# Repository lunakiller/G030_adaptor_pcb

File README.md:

# STM32G030F6P6 Adaptor PCB

Adaptor PCB for STM32G030F6P6. Contains power LED, 3.3V voltage regulator and SWD pin header for programming. 

All free pins are routed to the edge of the board.

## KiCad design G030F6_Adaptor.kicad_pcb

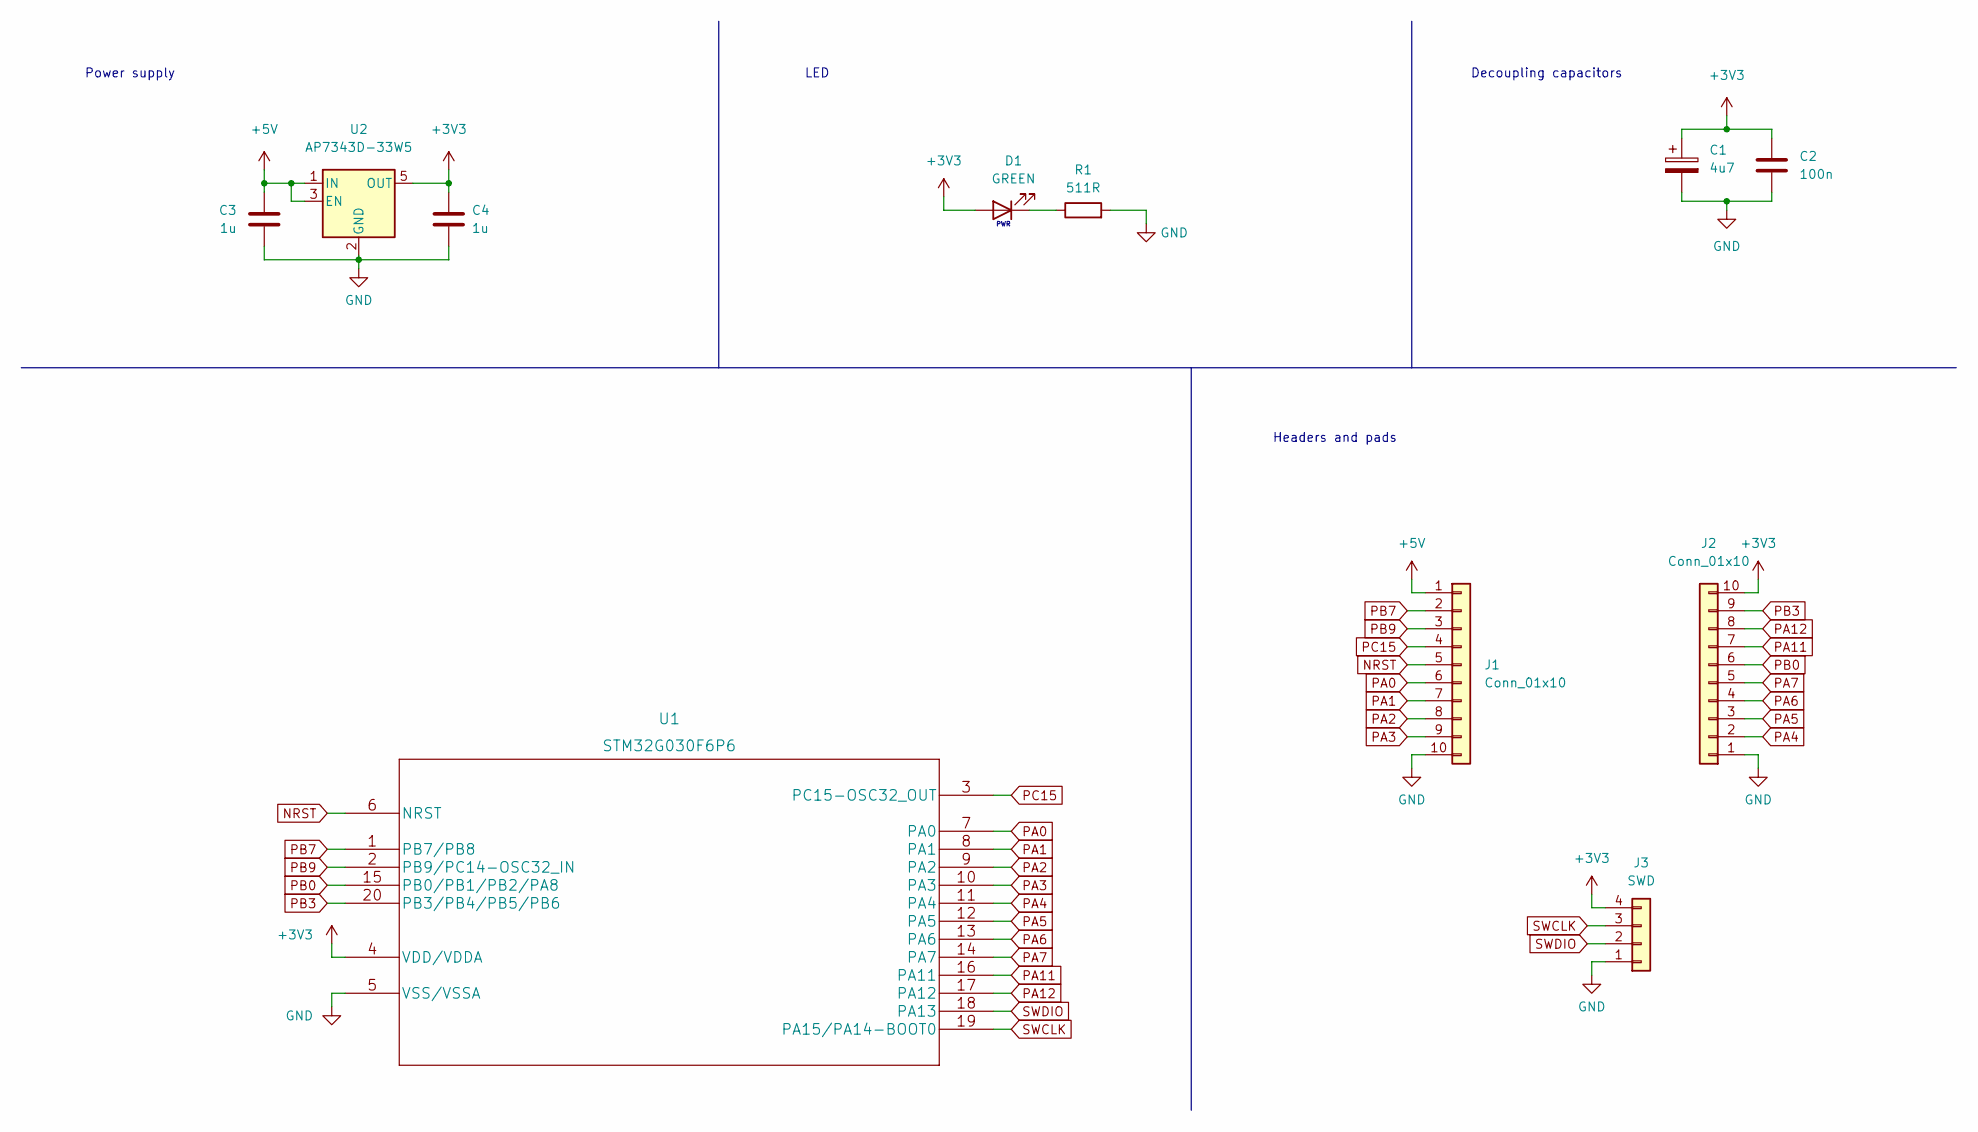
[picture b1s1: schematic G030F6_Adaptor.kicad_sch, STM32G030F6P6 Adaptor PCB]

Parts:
C1: 4u7; CP_EIA-1608-10_AVX-L
C2: 100n; C_0603_1608Metric
C3, C4: 1u; C_0603_1608Metric
D1: GREEN; LED_0603_1608Metric
J1, J2: Conn_01x10; PinHeader_Castellated_1x10_P2.54mm_Vertical
J3: SWD; PinHeader_1x04_P2.54mm_Vertical
R1: 511R; R_0603_1608Metric
U1: STM32G030F6P6; TSSOP-20_4.4x6.5mm_P0.65mm
U2: AP7343D-33W5; SOT-23-5

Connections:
+3V3: C1.1, C2.1, C4.1, D1.2 (A), J2.10, J3.4, U1.4 (VDD/VDDA), U2.5 (OUT)
+5V: C3.1, J1.1, U2.1 (IN), U2.3 (EN)
GND: C1.2, C2.2, C3.2, C4.2, J1.10, J2.1, J3.1, R1.2, U1.5 (VSS/VSSA), U2.2 (GND)
NRST: J1.5, U1.6 (NRST)
unnamed: D1.1 (K), R1.1
PA0: J1.6, U1.7 (PA0)
PA1: J1.7, U1.8 (PA1)
PA2: J1.8, U1.9 (PA2)
PA3: J1.9, U1.10 (PA3)
PA4: J2.2, U1.11 (PA4)
PA5: J2.3, U1.12 (PA5)
PA6: J2.4, U1.13 (PA6)
PA7: J2.5, U1.14 (PA7)
PA11: J2.7, U1.16 (PA11)
PA12: J2.8, U1.17 (PA12)
PB0: J2.6, U1.15 (PB0/PB1/PB2/PA8)
PB3: J2.9, U1.20 (PB3/PB4/PB5/PB6)
PB7: J1.2, U1.1 (PB7/PB8)
PB9: J1.3, U1.2 (PB9/PC14-OSC32_IN)
PC15: J1.4, U1.3 (PC15-OSC32_OUT)
SWCLK: J3.3, U1.19 (PA15/PA14-BOOT0)
SWDIO: J3.2, U1.18 (PA13)

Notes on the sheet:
Decoupling capacitors
Headers and pads
LED
Power supply
PWR

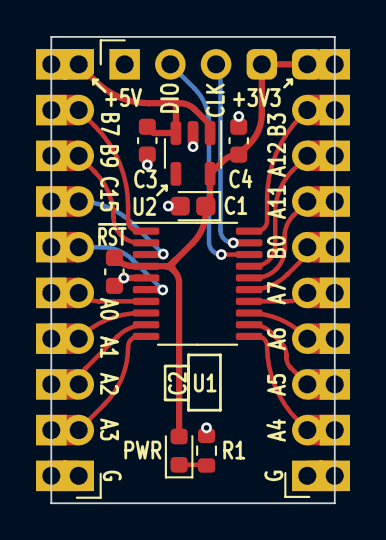
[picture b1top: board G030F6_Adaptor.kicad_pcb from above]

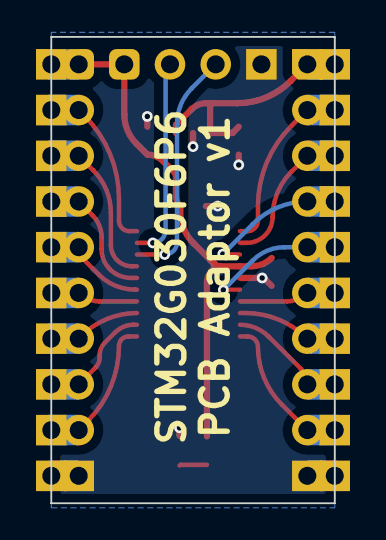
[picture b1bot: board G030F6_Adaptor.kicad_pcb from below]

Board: 2 copper layers, 15.7 x 25.9 mm, 11 parts (2 on the bottom side), 22 nets.

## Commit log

2022-07-27 Upload files
2022-07-27 Small addition
2022-07-27 Added LICENSE
2022-08-17 Track correction, resistor values, updated visualization
